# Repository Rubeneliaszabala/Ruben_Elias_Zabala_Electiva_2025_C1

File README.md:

# Ruben_Elias_Zabala_Electiva_2025_C1

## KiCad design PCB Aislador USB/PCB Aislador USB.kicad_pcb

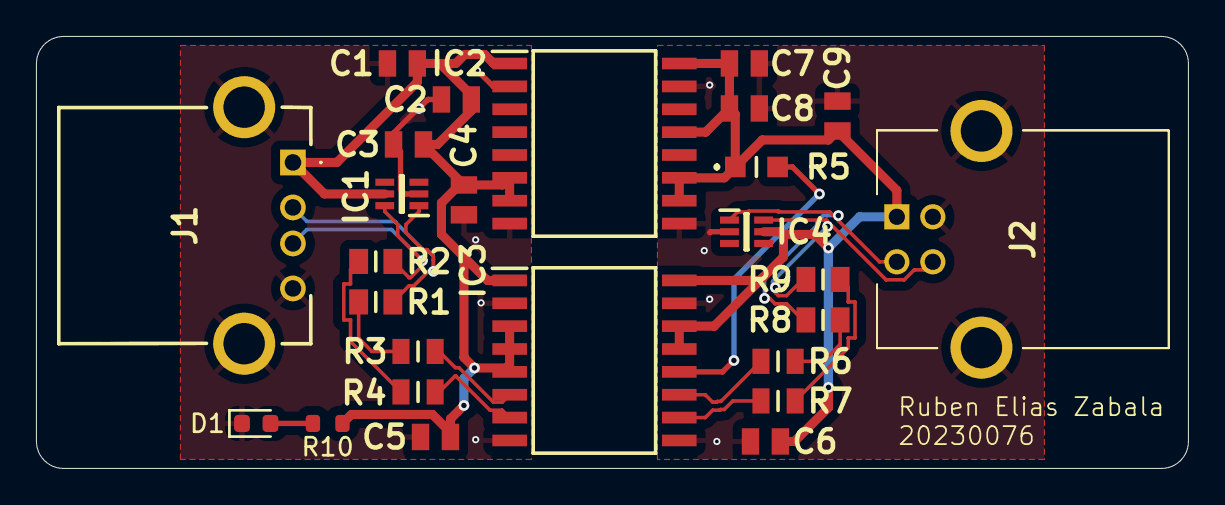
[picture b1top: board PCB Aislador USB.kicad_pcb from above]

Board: 2 copper layers, 64.0 x 24.0 mm, 26 parts (0 on the bottom side), 18 nets.

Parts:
C1, C8: GRM21BR61C106KE15L; CAPC2012X145N
C2, C3, C4, C5, C6, C7, C9: GRM21BR71H104KA01L; CAPC2012X145N
D1: Green; D_0603
IC1, IC4: NUP2202W1T2G; SOT65P210X110-6N
IC2: ADUM5000ARWZ; SOIC127P1032X265-16N
IC3: ADUM3160BRWZ; SOIC127P1032X265-16N
J1: 87520-0010BLF; 875200010BLF
J2: USB-B-S-F-B-TH-R; USBBSFBTHR
R1, R2, R8, R9: ERJ-6GEY0R00V; RESC2012X70N
R3, R4, R6, R7: RT0805FRE0724RL; RESC2012X60N
R5: ERJ-6ENF1002V; ERJ6ENF1000V
R10: 100Ω; R_0603

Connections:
+5V: C1.1, C2.1, C3.1, C4.1, C5.1, IC1.5 (VP), IC2.1 (VDD1_1), IC2.6 (RCSEL), IC2.7 (VDD1_2), IC3.1 (VBUS1), IC3.3 (VDD1), IC3.4 (PDEN), IC3.5 (SPU), J1.1, R10.1
/USB_+_11: IC1.6 (I/O_2), J1.3, R2.1
/USB_+_12: R2.2, R4.1
/USB_+_13: IC3.7 (UD+), R4.2
/USB_+_21: IC4.6 (I/O_2), J2.3, R9.2
/USB_+_22: R7.2, R9.1
/USB_+_23: IC3.10 (DD+), R7.1
/USB_-_11: IC1.1 (I/O_1), J1.2, R1.1
/USB_-_12: R1.2, R3.1
/USB_-_13: IC3.6 (UD-), R3.2
/USB_-_21: IC4.1 (I/O_1), J2.2, R8.2
/USB_-_22: R6.2, R8.1
/USB_-_23: IC3.11 (DD-), R6.1
GND_A: C1.2, C2.2, C3.2, C4.2, C5.2, D1.1, IC1.2 (VN), IC2.2 (GND1_1), IC2.8 (GND1_2), IC3.2 (GND1_1), IC3.8 (GND1_2), J1.4, J1.MH1, J1.MH2
GND_B: C6.2, C7.2, C8.2, C9.2, IC2.9 (GNDISO_1), IC2.15 (GNDISO_2), IC3.9 (GND2_1), IC3.15 (GND2_2), IC4.2 (VN), J2.4, J2.MH1, J2.MH2
unnamed: D1.2, R10.2
unnamed: IC3.12 (PIN), R5.2
VISO: C6.1, C7.1, C8.1, C9.1, IC2.10 (VISO_1), IC2.11 (NC_2), IC2.13 (VSEL), IC2.16 (VISO_2), IC3.13 (SPD), IC3.14 (VDD2), IC3.16 (VBUS2), IC4.5 (VP), J2.1, R5.1

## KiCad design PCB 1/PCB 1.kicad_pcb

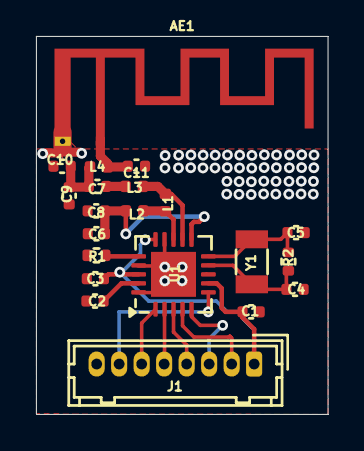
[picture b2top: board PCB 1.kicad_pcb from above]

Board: 2 copper layers, 16.2 x 21.0 mm, 21 parts (0 on the bottom side), 18 nets.

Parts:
AE1: Antenna; Texas_SWRA117D_2.4GHz_Right
C1: 10n; C_0402_1005Metric
C2: 33n; C_0402_1005Metric
C3: 1n; C_0402_1005Metric
C4, C5: 22p; C_0402_1005Metric
C6, C8: C_0402_1005Metric
C7: 1p5; C_0402_1005Metric
C9: 1p; C_0402_1005Metric
C10, C11: Cx; C_0402_1005Metric
J1: Conn_01x08_Pin; Hirose_DF13-08P-1.25DSA_1x08_P1.25mm_Vertical
L1: 8n2; L_0402_1005Metric
L2: 2n7; L_0402_1005Metric
L3: 3n9; L_0402_1005Metric
L4: Lx; L_0402_1005Metric
R1: 22k; R_0402_1005Metric
R2: 10M; R_0402_1005Metric
U1: NRF24L01; QFN-20-1EP_4x4mm_P0.5mm_EP2.5x2.5mm
Y1: 16MHz; Crystal_SMD_3215-2Pin_3.2x1.5mm

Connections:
GND: C1.2, C2.2, C3.2, C4.2, C5.2, C6.2, C8.2, C9.2, C10.2, C11.2, J1.8, R1.2, U1.8 (VSS), U1.14 (VSS), U1.17 (VSS), U1.20 (VSS)
unnamed: AE1.1 (A), C11.1, L4.2
unnamed: C7.1, L3.2
unnamed: C7.2, C9.1, C10.1, L4.1
unnamed: J1.2, U1.4 (MOSI)
unnamed: J1.3, U1.5 (MISO)
unnamed: J1.4, U1.3 (SCK)
unnamed: J1.5, U1.2 (CSN)
unnamed: J1.6, U1.1 (CE)
unnamed: J1.7, U1.6 (IRQ)
unnamed: L1.1, L3.1, U1.12 (ANT1)
unnamed: L1.2, L2.1, U1.13 (ANT2)
unnamed: C2.1, U1.19 (DVDD)
unnamed: R1.1, U1.16 (IREF)
unnamed: C6.1, C8.1, L2.2, U1.11 (VDD_PA)
unnamed: C5.1, R2.2, U1.10 (XC1), Y1.2
unnamed: C4.1, R2.1, U1.9 (XC2), Y1.1
VDD: C1.1, C3.1, J1.1, U1.7 (VDD), U1.15 (VDD), U1.18 (VDD)

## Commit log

2025-03-21 Create PCB Aislador
